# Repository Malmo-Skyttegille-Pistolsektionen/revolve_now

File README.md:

<h1></h1>

Software for running timed shooting programs on a rotating target system, built
by and for Malmö Skyttegille Pistolsektionen.

An ESP32-S3 board turns the targets face-on and edge-on to a shooting program
and plays the spoken range commands over an amplifier. A React web app — served
by the board itself over WiFi — starts and stops programs, follows the run live
over Server-Sent Events, and manages the stored programs and audio.

## ⚠️ SAFETY WARNING — READ BEFORE INSTALLING OR OPERATING

**This device moves steel on a live firing range, and it moves it on a timer.**
A target turns because a program said it was time, not because it can see who
is in front of it. It has no idea anyone is downrange.

- **The range's own safety rules and range commands govern the line. This
  software governs nothing.** A program running is not a range that is hot; a
  program stopped is not a range that is safe.
- **NEVER go downrange because the web app says the run has finished.** Confirm
  a cease-fire the way your range already requires — verbally, with firearms
  cleared and benched.
- **NEVER leave the device powered while people are forward of the firing
  line** unless your club has decided that is safe and knows what the targets
  do at power-up.
- **A target turning can injure somebody standing next to it.** Keep clear of
  the mechanism whenever the device is powered.

The targets rest **shown** at boot, deliberately: a target that turns of its own
accord when a board is powered is the failure this project is most concerned
with. That resting state can be changed to suit a target system wired the other
way round, but only over a USB cable, never from the web app — see
[Expert mode](https://malmo-skyttegille-pistolsektionen.github.io/revolve_now/expert-mode/).

**Do not rely on this software to protect anyone.** It is a convenience for
running programs, not a safety device, and it has no interlock, no sensor, and
no way to know where people are.

**LIABILITY DISCLAIMER:** This project is provided as-is with absolutely no
warranty of any kind. The author(s) accept no responsibility or liability for
any injury, damage, or loss resulting from building, installing, modifying, or
operating this system. You build and use it entirely at your own risk.

---

## Documentation

Everything an operator needs is on the documentation site, in English and
Swedish (the language menu in the header switches):

- **[Operator documentation](https://malmo-skyttegille-pistolsektionen.github.io/revolve_now/)**
  — wiring, connecting, running a program, settings, and what the status LED is
  telling you. This is the one to send a club member.
- **[Program editor](https://malmo-skyttegille-pistolsektionen.github.io/revolve_now/editor/)**
  — write and edit programs in a browser with **no device attached**, then
  download the file or open a pull request against this repository. Also useful
  for reading a shipped program without a board in front of you.
- **[Hardware and wiring](https://malmo-skyttegille-pistolsektionen.github.io/revolve_now/hardware/)**
  — what a target system has to do to work, the DB9 pinout, and the transistor
  that does the switching.

## Installing

Releases ship a pre-built firmware image; you do not need a toolchain to put it
on a board. See
[Connecting](https://malmo-skyttegille-pistolsektionen.github.io/revolve_now/connecting/)
for getting the device onto your network afterwards, and
[Settings](https://malmo-skyttegille-pistolsektionen.github.io/revolve_now/settings/)
for adapting a stock image to your own board — the target pin, its polarity,
the audio and LED pins and the device's name are all configurable on the
device, without rebuilding it.

## Target systems

- **[Eigenbrod TP2](https://eigenbrod-schiessanlagen.de/en/products?tx_produkt_produkte%5Baction%5D=show&tx_produkt_produkte%5BL%5D=2&tx_produkt_produkte%5Bprodukt%5D=319&cHash=942340d5971be0a0ac3d26ff3c257c0b)**
  — what this was built against and what it runs on.

Nothing in the firmware is specific to that system. The board speaks no
proprietary protocol to the targets: it closes and opens **one circuit**, and
the target system's own electronics do the rest. Any system driven the same way
should work.

## Layout

| Directory | Holds |
|---|---|
| [`contracts/`](contracts/README.md) | The canonical API contract: OpenAPI for REST v2, AsyncAPI for SSE v2, the program schema |
| [`firmware/`](firmware/README.md) | The ESP-IDF firmware: target IO, audio, storage, REST + SSE server |
| [`webapp/`](webapp/README.md) | The React front end, embedded in the firmware's application image |
| [`resources/`](resources/README.md) | Shipped programs and audio clips flashed onto the device |
| [`hardware/enclosure/`](hardware/enclosure/README.md) | A 3D-printable box for the rev 2 main board |
| [`docs/`](docs/) | The [decision log](docs/DECISIONS.md), [how releases are cut](docs/RELEASING.md), and the source of the documentation site |

## Contributing

Building, flashing, running it without a device, and the coding standards are
in [`CONTRIBUTING.md`](CONTRIBUTING.md).

## License

MIT — see [`LICENSE`](LICENSE). It covers everything here except the vendored
libraries under `firmware/lib/`, which keep their own.

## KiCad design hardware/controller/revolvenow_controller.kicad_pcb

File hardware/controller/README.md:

# Controller board

The Revolve Now controller board (the relay box), rev 2. It has no
microcontroller: eight LGE2300 N-channel MOSFETs (`Q1`–`Q8`) switch the target
outputs low, driven from the inputs on `J9`. The board is two halves, labelled
**1–2** and **3–4** on the silkscreen, each with its own USB-C power input,
output RJ45 and output header. 95 × 50 mm, two copper layers.

## Connectors

| Ref | Part | Role |
|---|---|---|
| `J3` | RJ45 | Outputs of half 1–2: the drains of `Q1`–`Q4` on pins 1, 3, 5, 7, ground on 2, 4, 6, 8 |
| `J5` | RJ45 | Outputs of half 3–4, the same way, from `Q5`–`Q8` |
| `J4`, `J6` | 1×6 pin header | +5 V, GND and the four outputs of half 1–2 and 3–4 |
| `J7`, `J8` | USB-C | 5 V power for half 1–2 and 3–4. Power only: the data lines are not connected |
| `J9` | RJ45 | Manual remote control: +5 V on pins 1, 3, 5, 7, MOSFET gates on 2, 4, 6, 8 |
| `J1`, `J2` | 2×2 pin header | Jumpers that join the +5 V (`J1`) and the GND (`J2`) of the two halves. `R1` and `R2`, 0 Ω and not fitted, do the same |

Each `J9` pair drives two MOSFETs, so one input switches two outputs:

| `J9` pins | MOSFETs | Outputs |
|---|---|---|
| 1–2 | `Q1`, `Q3` | `J3` pins 1 and 5 |
| 3–4 | `Q2`, `Q4` | `J3` pins 3 and 7 |
| 5–6 | `Q5`, `Q7` | `J5` pins 1 and 5 |
| 7–8 | `Q6`, `Q8` | `J5` pins 3 and 7 |

## Files

| Path | What it is |
|---|---|
| `revolvenow_controller.kicad_pro` | The KiCad project. Open this one, in KiCad 10 |
| `revolvenow_controller.kicad_sch` | Root schematic: the Controller sheet, and `power1.kicad_sch` and `output1.kicad_sch` each used twice, once per half |
| `revolvenow_controller.kicad_pcb` | The board |
| `fab/rev2/` | What was sent to the fab, described in the [hardware README](../README.md#fabrication-output) |

Footprints from the shared library come from [`../lib/`](../lib/) through
`fp-lib-table`.

Open items in the design are tracked in the
[rev 2 review on #603](https://github.com/Malmo-Skyttegille-Pistolsektionen/revolve_now/pull/603#issuecomment-6858837484).

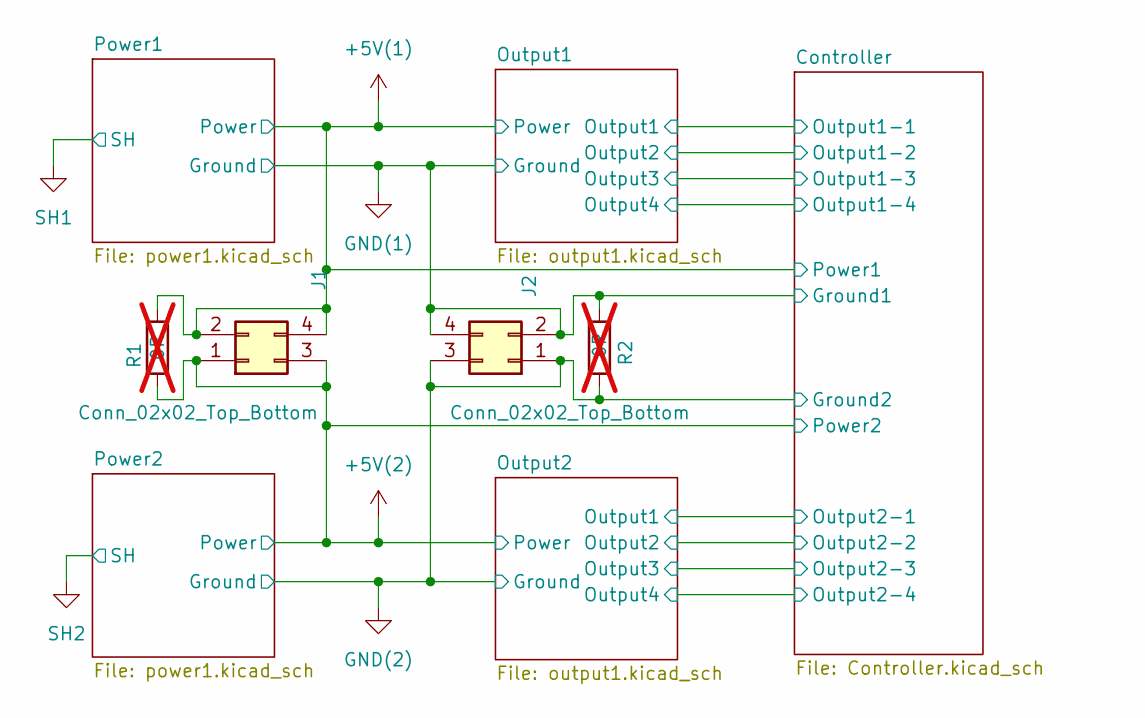
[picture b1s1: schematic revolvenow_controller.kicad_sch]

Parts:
J1, J2: Conn_02x02_Top_Bottom; PinHeader_2x02_P2.54mm_Vertical
R1, R2: 0R; R_0603_1608Metric_Pad0.98x0.95mm_HandSolder; not fitted

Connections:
+5V(1): J1.2, J1.4, R1.1; also elsewhere on the board
+5V(2): J1.1, J1.3, R1.2; also elsewhere on the board
GND(1): J2.2, J2.4, R2.2; also elsewhere on the board
GND(2): J2.1, J2.3, R2.1; also elsewhere on the board

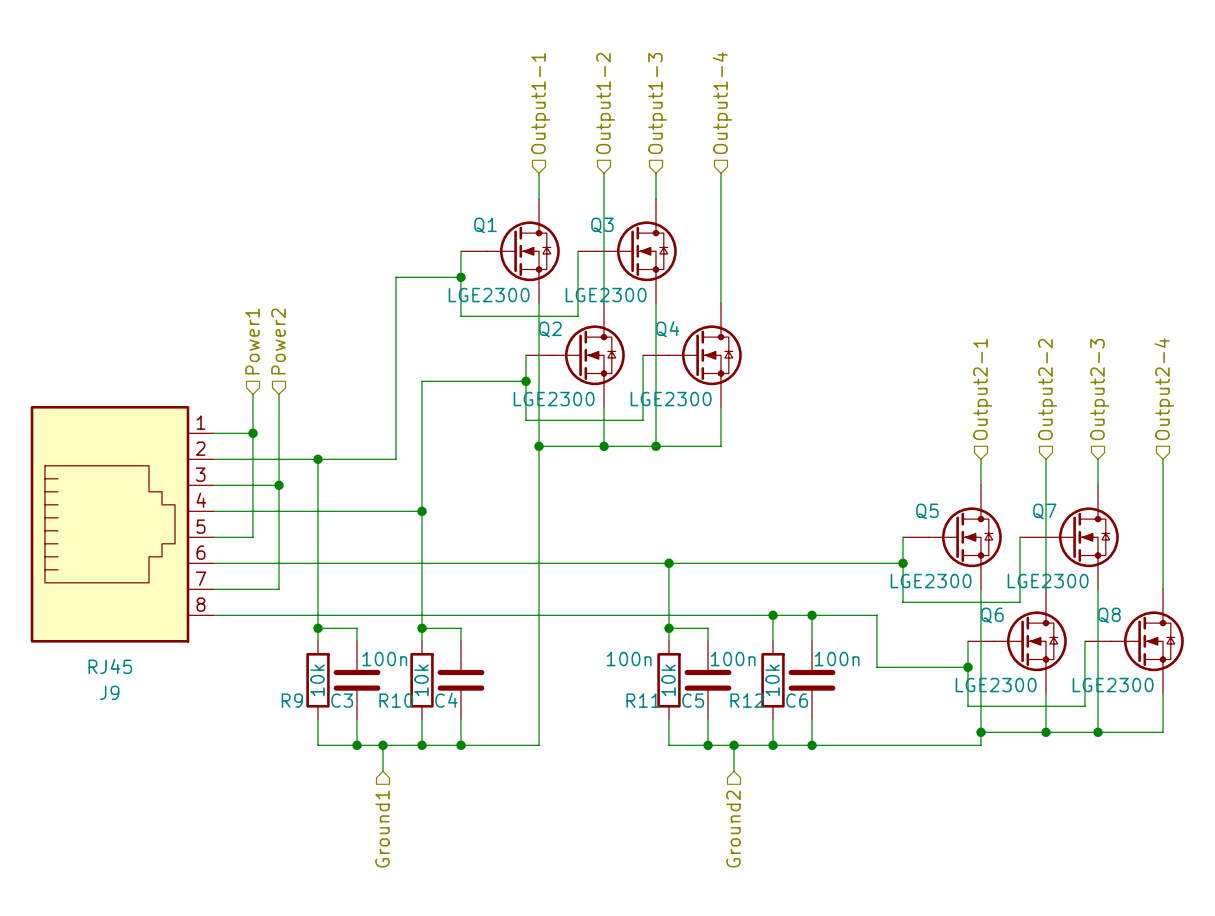
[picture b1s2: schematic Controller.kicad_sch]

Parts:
C3, C4, C5, C6: 100n; C_0603_1608Metric_Pad1.08x0.95mm_HandSolder
J9: RJ45
Q1, Q2, Q3, Q4, Q5, Q6, Q7, Q8: LGE2300; SOT-23
R9, R10, R11, R12: 10k; R_0603_1608Metric_Pad0.98x0.95mm_HandSolder

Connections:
+5V(1): J9.1, J9.5; also elsewhere on the board
+5V(2): J9.3, J9.7; also elsewhere on the board
/Controller/Output1-1: Q1.3 (D); also elsewhere on the board
/Controller/Output1-2: Q2.3 (D); also elsewhere on the board
/Controller/Output1-3: Q3.3 (D); also elsewhere on the board
/Controller/Output1-4: Q4.3 (D); also elsewhere on the board
/Controller/Output2-1: Q5.3 (D); also elsewhere on the board
/Controller/Output2-2: Q6.3 (D); also elsewhere on the board
/Controller/Output2-3: Q7.3 (D); also elsewhere on the board
/Controller/Output2-4: Q8.3 (D); also elsewhere on the board
GND(1): C3.2, C4.2, Q1.2 (S), Q2.2 (S), Q3.2 (S), Q4.2 (S), R9.1, R10.1; also elsewhere on the board
GND(2): C5.2, C6.1, Q5.2 (S), Q6.2 (S), Q7.2 (S), Q8.2 (S), R11.1, R12.1; also elsewhere on the board
unnamed: C3.1, J9.2, Q1.1 (G), Q3.1 (G), R9.2
unnamed: C4.1, J9.4, Q2.1 (G), Q4.1 (G), R10.2
unnamed: C5.1, J9.6, Q5.1 (G), Q7.1 (G), R11.2
unnamed: C6.2, J9.8, Q6.1 (G), Q8.1 (G), R12.2

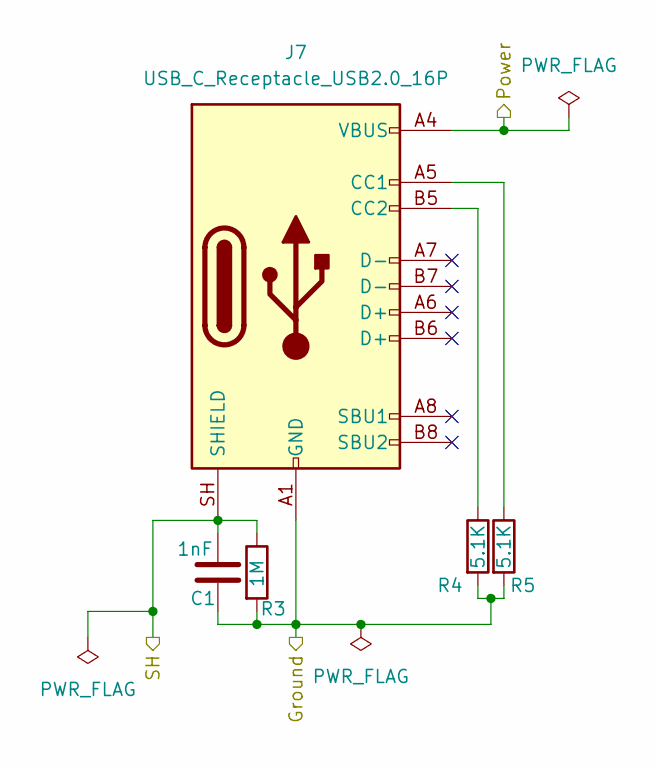
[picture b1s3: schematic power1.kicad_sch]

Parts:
C1: 1nF; C_0603_1608Metric_Pad1.08x0.95mm_HandSolder
J7: USB_C_Receptacle_USB2.0_16P; USB Type-C-02
R3: 1M; R_0603_1608Metric_Pad0.98x0.95mm_HandSolder
R4, R5: 5.1K; R_0603_1608Metric_Pad0.98x0.95mm_HandSolder

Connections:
+5V(1): J7.A4 (VBUS), J7.B4 (VBUS); also elsewhere on the board
GND(1): C1.2, J7.A1 (GND), J7.B1 (GND), R3.2, R4.2, R5.2; also elsewhere on the board
unnamed: J7.A5 (CC1), R5.1
unnamed: J7.B5 (CC2), R4.1
SH1: C1.1, J7.SH (SHIELD), R3.1

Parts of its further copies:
C2: 1nF; C_0603_1608Metric_Pad1.08x0.95mm_HandSolder
J8: USB_C_Receptacle_USB2.0_16P; USB Type-C-02
R6: 1M; R_0603_1608Metric_Pad0.98x0.95mm_HandSolder
R7, R8: 5.1K; R_0603_1608Metric_Pad0.98x0.95mm_HandSolder

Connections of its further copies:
+5V(2): J8.A4 (VBUS), J8.B4 (VBUS); also elsewhere on the board
GND(2): C2.2, J8.A1 (GND), J8.B1 (GND), R6.2, R7.2, R8.2; also elsewhere on the board
unnamed: J8.A5 (CC1), R8.1
unnamed: J8.B5 (CC2), R7.1
SH2: C2.1, J8.SH (SHIELD), R6.1

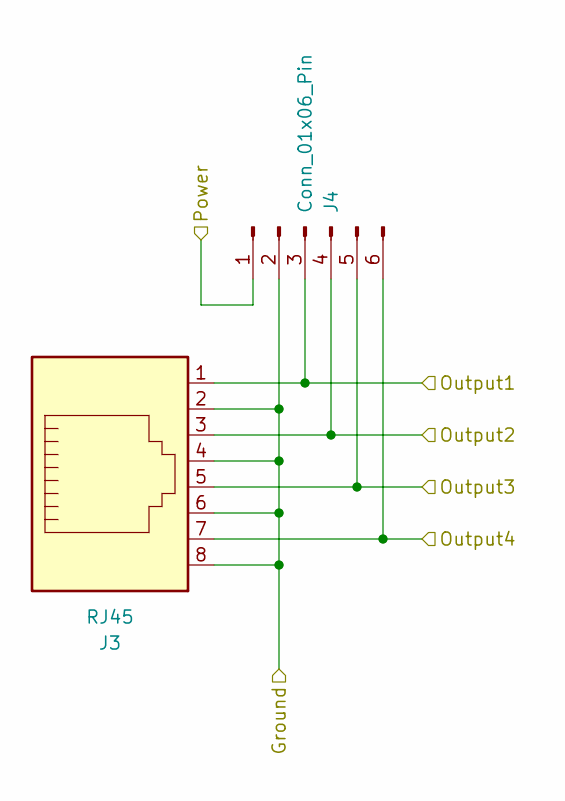
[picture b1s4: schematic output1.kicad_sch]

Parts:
J3: RJ45
J4: Conn_01x06_Pin; PinHeader_1x06_P2.54mm_Vertical

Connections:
+5V(1): J4.1; also elsewhere on the board
/Controller/Output1-1: J3.1, J4.3; also elsewhere on the board
/Controller/Output1-2: J3.3, J4.4; also elsewhere on the board
/Controller/Output1-3: J3.5, J4.5; also elsewhere on the board
/Controller/Output1-4: J3.7, J4.6; also elsewhere on the board
GND(1): J3.2, J3.4, J3.6, J3.8, J4.2; also elsewhere on the board

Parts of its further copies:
J5: RJ45
J6: Conn_01x06_Pin; PinHeader_1x06_P2.54mm_Vertical

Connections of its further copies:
+5V(2): J6.1; also elsewhere on the board
/Controller/Output2-1: J5.1, J6.3; also elsewhere on the board
/Controller/Output2-2: J5.3, J6.4; also elsewhere on the board
/Controller/Output2-3: J5.5, J6.5; also elsewhere on the board
/Controller/Output2-4: J5.7, J6.6; also elsewhere on the board
GND(2): J5.2, J5.4, J5.6, J5.8, J6.2; also elsewhere on the board

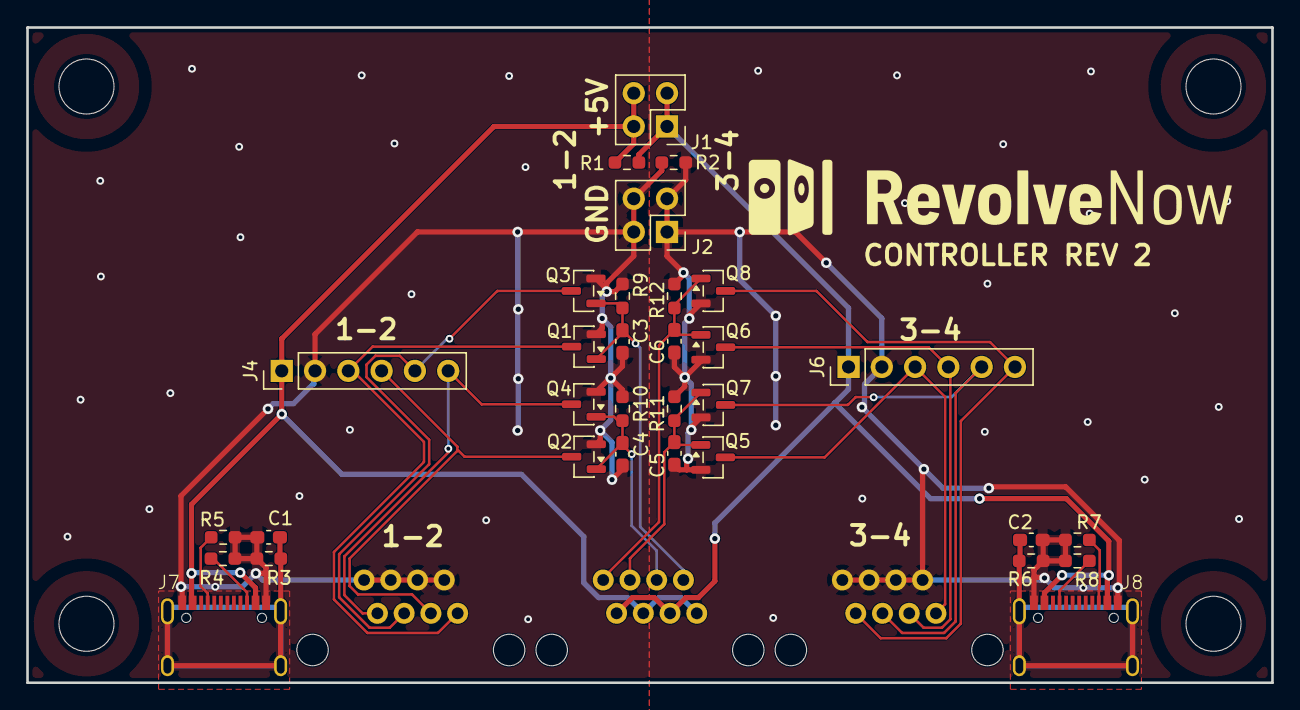
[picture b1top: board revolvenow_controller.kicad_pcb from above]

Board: 2 copper layers, 95.0 x 50.0 mm, 35 parts (0 on the bottom side), 22 nets.

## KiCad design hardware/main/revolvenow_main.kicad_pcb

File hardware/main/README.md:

# Main board

The Revolve Now main board, rev 2. An ESP32-S3-WROOM-1 (`U1`) drives sixteen
opto-isolated target outputs, reads two opto-isolated trigger inputs, talks to
the network over WiFi or a W5500 Ethernet controller (`U10`), and plays the
range commands through a PCM5102A DAC (`U2`). One WS2812B (`D8`) is the status
LED. 100 × 100 mm, two copper layers.

## Connectors

| Ref | Part | Role |
|---|---|---|
| `J1`, `J2`, `J6`, `J8` | RJ45 | Target outputs Turn 0–3, 4–7, 8–11 and 12–15, through the LTV-847 optocouplers `U4`, `U5`, `U7` and `U8` |
| `J3` | RJ45 | Trigger inputs through the LTV-847 `U3`: pins 1–2 for a 5 V signal, pins 3–6 for 12 V |
| `J4` | USB-C | 5 V power, and the ESP32-S3's native USB (GPIO19/20) behind the USBLC6-2SC6 `U12` |
| `J5` | 1×3 pin header | UART0: RX, GND, TX |
| `J7` | 3.5 mm jack (PJ-320A) | Line out from the DAC |
| `J9` | 2×3 pin header | Jumper that puts GPIO4 on the status LED data (pins 1–2), trigger 0 (3–4) or trigger 1 (5–6) |
| `U11` | RJ45 with magnetics (J0026D21BNL) | Ethernet, from the W5500 |

Each output RJ45 carries four outputs, one per twisted pair, each the
transistor side of one optocoupler channel with the collector on the odd pin:

| Pins | Output |
|---|---|
| 1–2 | first (Turn 0, 4, 8, 12) |
| 3–6 | second |
| 4–5 | third |
| 7–8 | fourth (Turn 3, 7, 11, 15) |

The two buttons are `SW2` (FLASH, on GPIO0) and `SW3` (RESET, on EN).

## Files

| Path | What it is |
|---|---|
| `revolvenow_main.kicad_pro` | The KiCad project. Open this one, in KiCad 10 |
| `revolvenow_main.kicad_sch` | Root schematic, with one sheet per function: ESP, Power, USB, Network, Audio, Output, Trigger, LED |
| `buttons.kicad_sch`, `flash.kicad_sch`, `temperature.kicad_sch` | Sheets no longer in the hierarchy |
| `revolvenow_main.kicad_pcb` | The board |
| `fab/rev2/` | What was sent to the fab, described in the [hardware README](../README.md#fabrication-output) |

Footprints from the shared library come from [`../lib/`](../lib/) through
`fp-lib-table`.

Open items in the design are tracked in the
[rev 2 review on #436](https://github.com/Malmo-Skyttegille-Pistolsektionen/revolve_now/pull/436#issuecomment-6858836932).

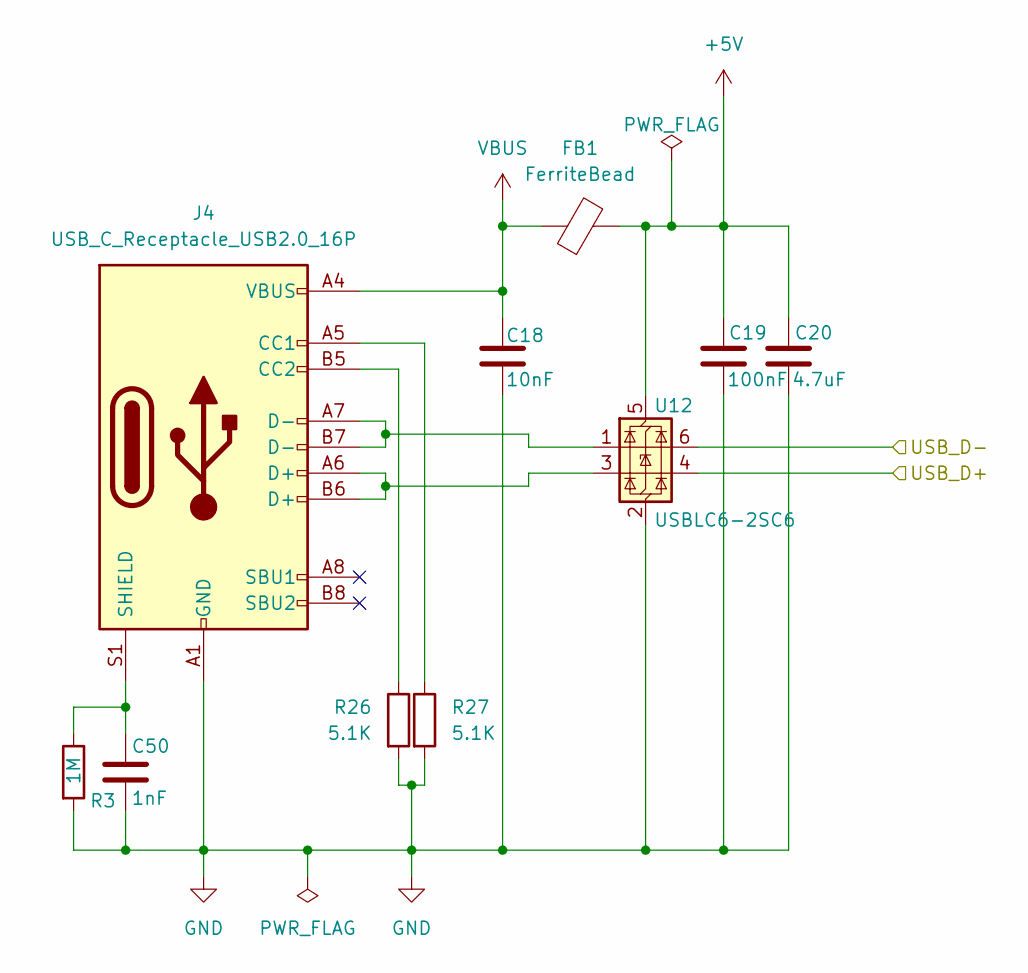
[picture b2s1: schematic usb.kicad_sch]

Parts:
C18: 10nF; C_0603_1608Metric_Pad1.08x0.95mm_HandSolder
C19: 100nF; C_0603_1608Metric_Pad1.08x0.95mm_HandSolder
C20: 4.7uF; C_0603_1608Metric_Pad1.08x0.95mm_HandSolder
C50: 1nF; C_0603_1608Metric_Pad1.08x0.95mm_HandSolder
FB1: FerriteBead; R_0805_2012Metric_Pad1.20x1.40mm_HandSolder
J4: USB_C_Receptacle_USB2.0_16P; USB Type-C-02
R3: 1M; R_0603_1608Metric_Pad0.98x0.95mm_HandSolder
R26, R27: 5.1K; R_0603_1608Metric_Pad0.98x0.95mm_HandSolder
U12: USBLC6-2SC6; SOT-23-6

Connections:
+5V: C19.1, C20.1, FB1.2, U12.5 (VBUS); also elsewhere on the board
/ESP/USB_D+: U12.4 (I/O2); also elsewhere on the board
/ESP/USB_D-: U12.6 (I/O1); also elsewhere on the board
GND: C18.2, C19.2, C20.2, C50.1, J4.A1 (GND), J4.B1 (GND), R3.2, R26.2, R27.2, U12.2 (GND); also elsewhere on the board
unnamed: J4.A5 (CC1), R27.1
unnamed: J4.B5 (CC2), R26.1
unnamed: J4.A6 (D+), J4.B6 (D+), U12.3 (I/O2)
unnamed: J4.A7 (D-), J4.B7 (D-), U12.1 (I/O1)
unnamed: C50.2, J4.S1 (SHIELD), R3.1
VBUS: C18.1, FB1.1, J4.A4 (VBUS), J4.B4 (VBUS)

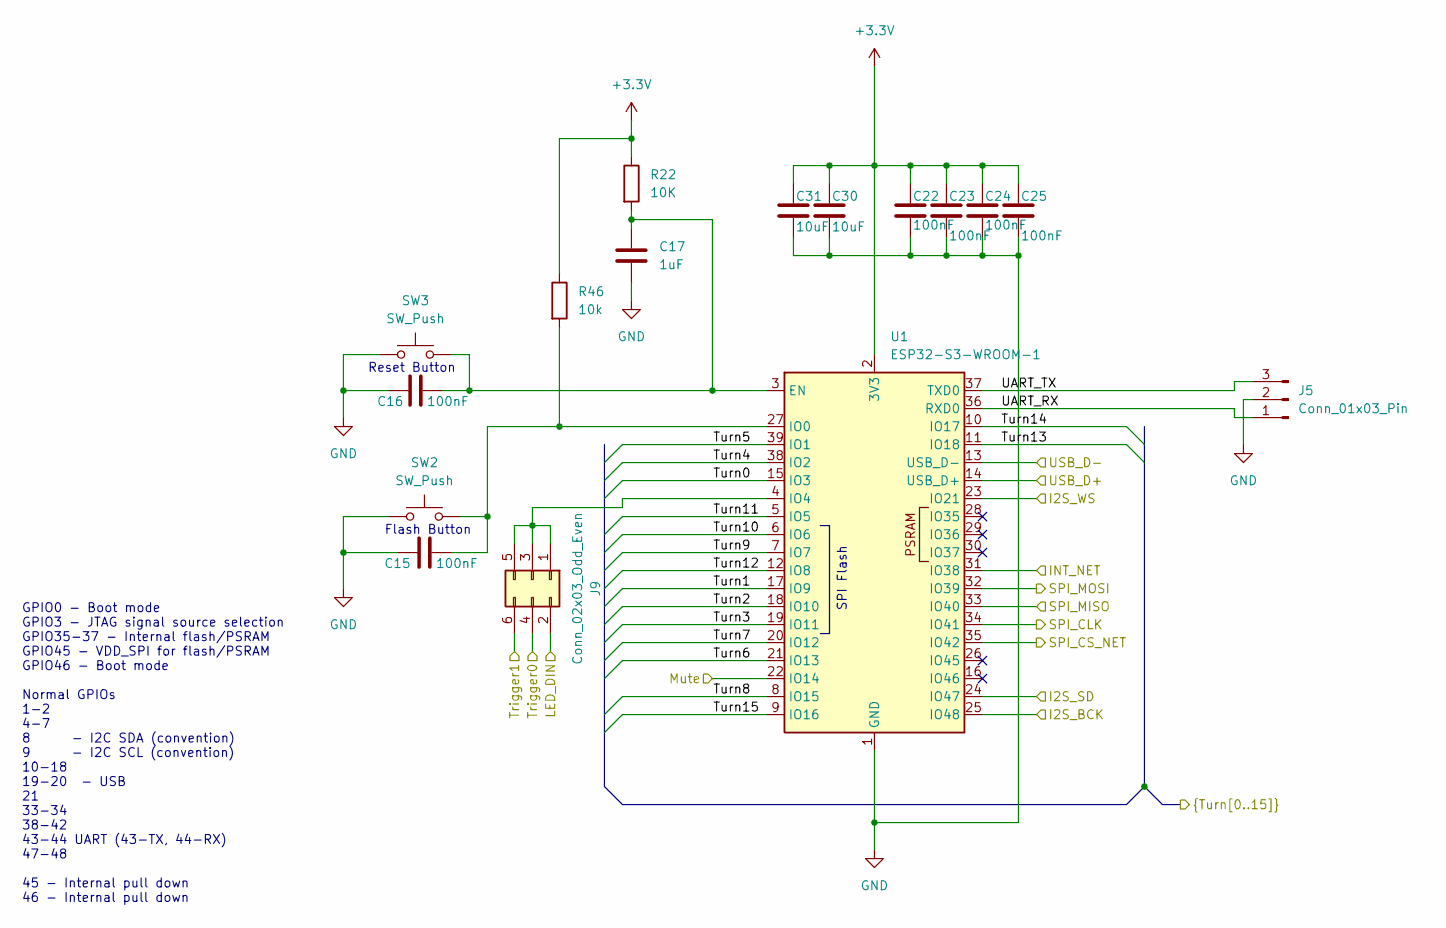
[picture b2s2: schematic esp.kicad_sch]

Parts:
C15, C16, C22, C23, C24, C25: 100nF; C_0603_1608Metric_Pad1.08x0.95mm_HandSolder
C17: 1uF; C_0603_1608Metric_Pad1.08x0.95mm_HandSolder
C30, C31: 10uF; C_0603_1608Metric_Pad1.08x0.95mm_HandSolder
J5: Conn_01x03_Pin; PinHeader_1x03_P2.54mm_Vertical
J9: Conn_02x03_Odd_Even; PinHeader_2x03_P2.54mm_Vertical
R22: 10K; R_0603_1608Metric_Pad0.98x0.95mm_HandSolder
R46: 10k; R_0603_1608Metric_Pad0.98x0.95mm_HandSolder
SW2, SW3: SW_Push; SW_SPST_PTS645Sx43SMTR92
U1: ESP32-S3-WROOM-1

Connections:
+3.3V: C22.1, C23.1, C24.1, C25.1, C30.1, C31.1, R22.1, R46.1, U1.2 (3V3); also elsewhere on the board
/Audio/BCK: U1.25 (IO48); also elsewhere on the board
/Audio/Mute: U1.22 (IO14); also elsewhere on the board
/Audio/SD: U1.24 (IO47); also elsewhere on the board
/Audio/WS: U1.23 (IO21); also elsewhere on the board
/ESP/INT_NET: U1.31 (IO38); also elsewhere on the board
/ESP/LED_DIN: J9.2; also elsewhere on the board
/ESP/SPI_CLK: U1.34 (IO41); also elsewhere on the board
/ESP/SPI_CS_NET: U1.35 (IO42); also elsewhere on the board
/ESP/SPI_MISO: U1.33 (IO40); also elsewhere on the board
/ESP/SPI_MOSI: U1.32 (IO39); also elsewhere on the board
/ESP/Trigger0: J9.4; also elsewhere on the board
/ESP/Trigger1: J9.6; also elsewhere on the board
/ESP/Turn0: U1.15 (IO3); also elsewhere on the board
/ESP/Turn1: U1.17 (IO9); also elsewhere on the board
/ESP/Turn2: U1.18 (IO10); also elsewhere on the board
/ESP/Turn3: U1.19 (IO11); also elsewhere on the board
/ESP/Turn4: U1.38 (IO2); also elsewhere on the board
/ESP/Turn5: U1.39 (IO1); also elsewhere on the board
/ESP/Turn6: U1.21 (IO13); also elsewhere on the board
/ESP/Turn7: U1.20 (IO12); also elsewhere on the board
/ESP/Turn8: U1.8 (IO15); also elsewhere on the board
/ESP/Turn9: U1.7 (IO7); also elsewhere on the board
/ESP/Turn10: U1.6 (IO6); also elsewhere on the board
/ESP/Turn11: U1.5 (IO5); also elsewhere on the board
/ESP/Turn12: U1.12 (IO8); also elsewhere on the board
/ESP/Turn13: U1.11 (IO18); also elsewhere on the board
/ESP/Turn14: U1.10 (IO17); also elsewhere on the board
/ESP/Turn15: U1.9 (IO16); also elsewhere on the board
/ESP/UART_RX: J5.1, U1.36 (RXD0)
/ESP/UART_TX: J5.3, U1.37 (TXD0)
/ESP/USB_D+: U1.14 (USB_D+); also elsewhere on the board
/ESP/USB_D-: U1.13 (USB_D-); also elsewhere on the board
GND: C15.1, C16.1, C17.2, C22.2, C23.2, C24.2, C25.2, C30.2, C31.2, J5.2, SW2.1, SW3.2, U1.1 (GND), U1.40 (GND), U1.41 (GND); also elsewhere on the board
unnamed: J9.1, J9.3, J9.5, U1.4 (IO4)
unnamed: C16.2, C17.1, R22.2, SW3.1, U1.3 (EN)
unnamed: C15.2, R46.2, SW2.2, U1.27 (IO0)

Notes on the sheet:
SPI Flash
Reset Button
Flash Button
GPIO0 - Boot mode GPIO3 - JTAG signal source selection GPIO35-37 - Internal flash/PSRAM GPIO45 - VDD_SPI for flash/PSRAM GPIO46 - Boot mode Normal GPIOs 1-2 4-7 8 - I2C SDA (convention) 9 - I2C SCL (convention) 10-18 19-20 - USB 21 33-34 38-42 43-44 UART (43-TX, 44-RX) 47-48 45 - Internal pull down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

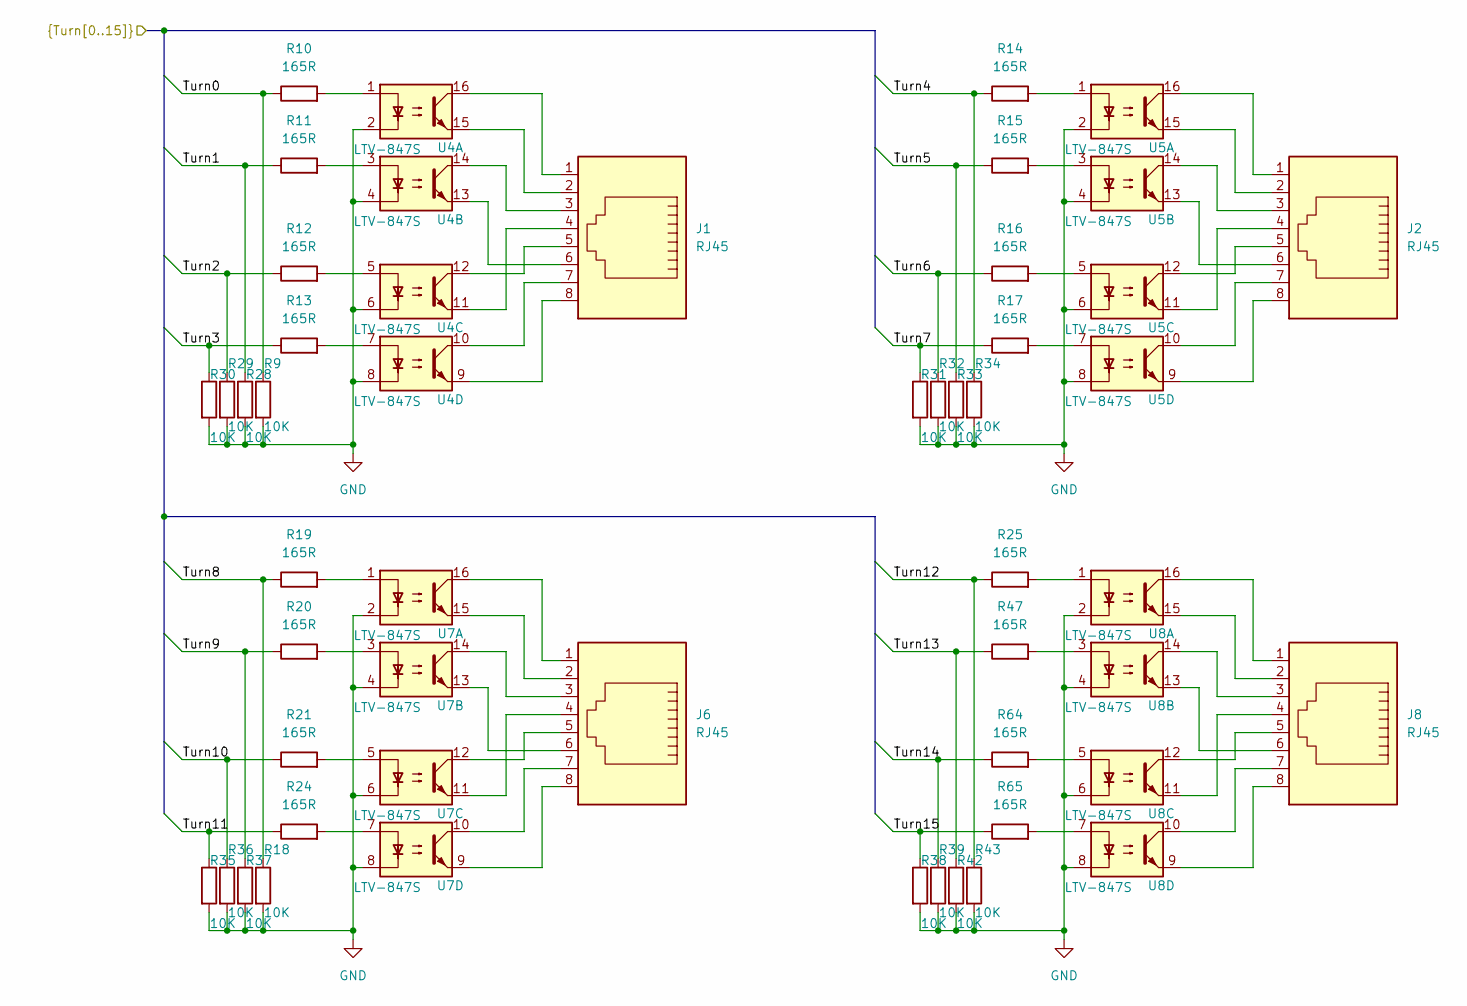
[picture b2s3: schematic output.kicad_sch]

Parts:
J1, J2, J6, J8: RJ45
R9, R18, R28, R29, R30, R31, R32, R33, R34, R35, R36, R37, R38, R39, R42, R43: 10K; R_0603_1608Metric_Pad0.98x0.95mm_HandSolder
R10, R11, R12, R13, R14, R15, R16, R17, R19, R20, R21, R24, R25, R47, R64, R65: 165R; R_0603_1608Metric_Pad0.98x0.95mm_HandSolder
U4, U5, U7, U8: LTV-847S; SMDIP-16_W9.53mm

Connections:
/ESP/Turn0: R9.1, R10.1; also elsewhere on the board
/ESP/Turn1: R11.1, R28.1; also elsewhere on the board
/ESP/Turn2: R12.1, R29.1; also elsewhere on the board
/ESP/Turn3: R13.1, R30.1; also elsewhere on the board
/ESP/Turn4: R14.1, R34.1; also elsewhere on the board
/ESP/Turn5: R15.1, R33.1; also elsewhere on the board
/ESP/Turn6: R16.1, R32.1; also elsewhere on the board
/ESP/Turn7: R17.1, R31.1; also elsewhere on the board
/ESP/Turn8: R18.1, R19.1; also elsewhere on the board
/ESP/Turn9: R20.1, R37.1; also elsewhere on the board
/ESP/Turn10: R21.1, R36.1; also elsewhere on the board
/ESP/Turn11: R24.1, R35.1; also elsewhere on the board
/ESP/Turn12: R25.1, R43.1; also elsewhere on the board
/ESP/Turn13: R42.1, R47.1; also elsewhere on the board
/ESP/Turn14: R39.1, R64.1; also elsewhere on the board
/ESP/Turn15: R38.1, R65.1; also elsewhere on the board
GND: R9.2, R18.2, R28.2, R29.2, R30.2, R31.2, R32.2, R33.2, R34.2, R35.2, R36.2, R37.2, R38.2, R39.2, R42.2, R43.2, U4.2, U4.4, U4.6, U4.8, U5.2, U5.4, U5.6, U5.8, U7.2, U7.4, U7.6, U7.8, U8.2, U8.4, U8.6, U8.8; also elsewhere on the board
unnamed: J1.1, U4.16
unnamed: J1.2, U4.15
unnamed: J1.3, U4.14
unnamed: J1.4, U4.11
unnamed: J1.5, U4.12
unnamed: J1.6, U4.13
unnamed: J1.7, U4.10
unnamed: J1.8, U4.9
unnamed: J2.1, U5.16
unnamed: J2.2, U5.15
unnamed: J2.3, U5.14
unnamed: J2.4, U5.11
unnamed: J2.5, U5.12
unnamed: J2.6, U5.13
unnamed: J2.7, U5.10
unnamed: J2.8, U5.9
unnamed: J6.1, U7.16
unnamed: J6.2, U7.15
unnamed: J6.3, U7.14
unnamed: J6.4, U7.11
unnamed: J6.5, U7.12
unnamed: J6.6, U7.13
unnamed: J6.7, U7.10
unnamed: J6.8, U7.9
unnamed: J8.1, U8.16
unnamed: J8.2, U8.15
unnamed: J8.3, U8.14
unnamed: J8.4, U8.11
unnamed: J8.5, U8.12
unnamed: J8.6, U8.13
unnamed: J8.7, U8.10
unnamed: J8.8, U8.9
unnamed: R10.2, U4.1
unnamed: R11.2, U4.3
unnamed: R12.2, U4.5
unnamed: R13.2, U4.7
unnamed: R14.2, U5.1
unnamed: R15.2, U5.3
unnamed: R16.2, U5.5
unnamed: R17.2, U5.7
unnamed: R19.2, U7.1
unnamed: R20.2, U7.3
unnamed: R21.2, U7.5
unnamed: R24.2, U7.7
unnamed: R25.2, U8.1
unnamed: R47.2, U8.3
unnamed: R64.2, U8.5
unnamed: R65.2, U8.7

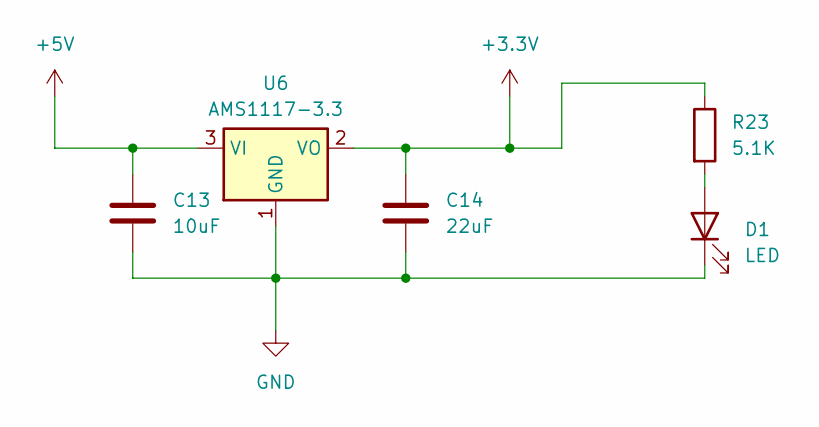
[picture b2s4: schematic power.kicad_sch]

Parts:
C13: 10uF; C_0603_1608Metric_Pad1.08x0.95mm_HandSolder
C14: 22uF; C_0603_1608Metric_Pad1.08x0.95mm_HandSolder
D1: LED; LED_0603_1608Metric_Pad1.05x0.95mm_HandSolder
R23: 5.1K; R_0603_1608Metric_Pad0.98x0.95mm_HandSolder
U6: AMS1117-3.3; SOT-223

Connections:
+3.3V: C14.1, R23.1, U6.2 (VO); also elsewhere on the board
+5V: C13.1, U6.3 (VI); also elsewhere on the board
GND: C13.2, C14.2, D1.1 (K), U6.1 (GND); also elsewhere on the board
unnamed: D1.2 (A), R23.2

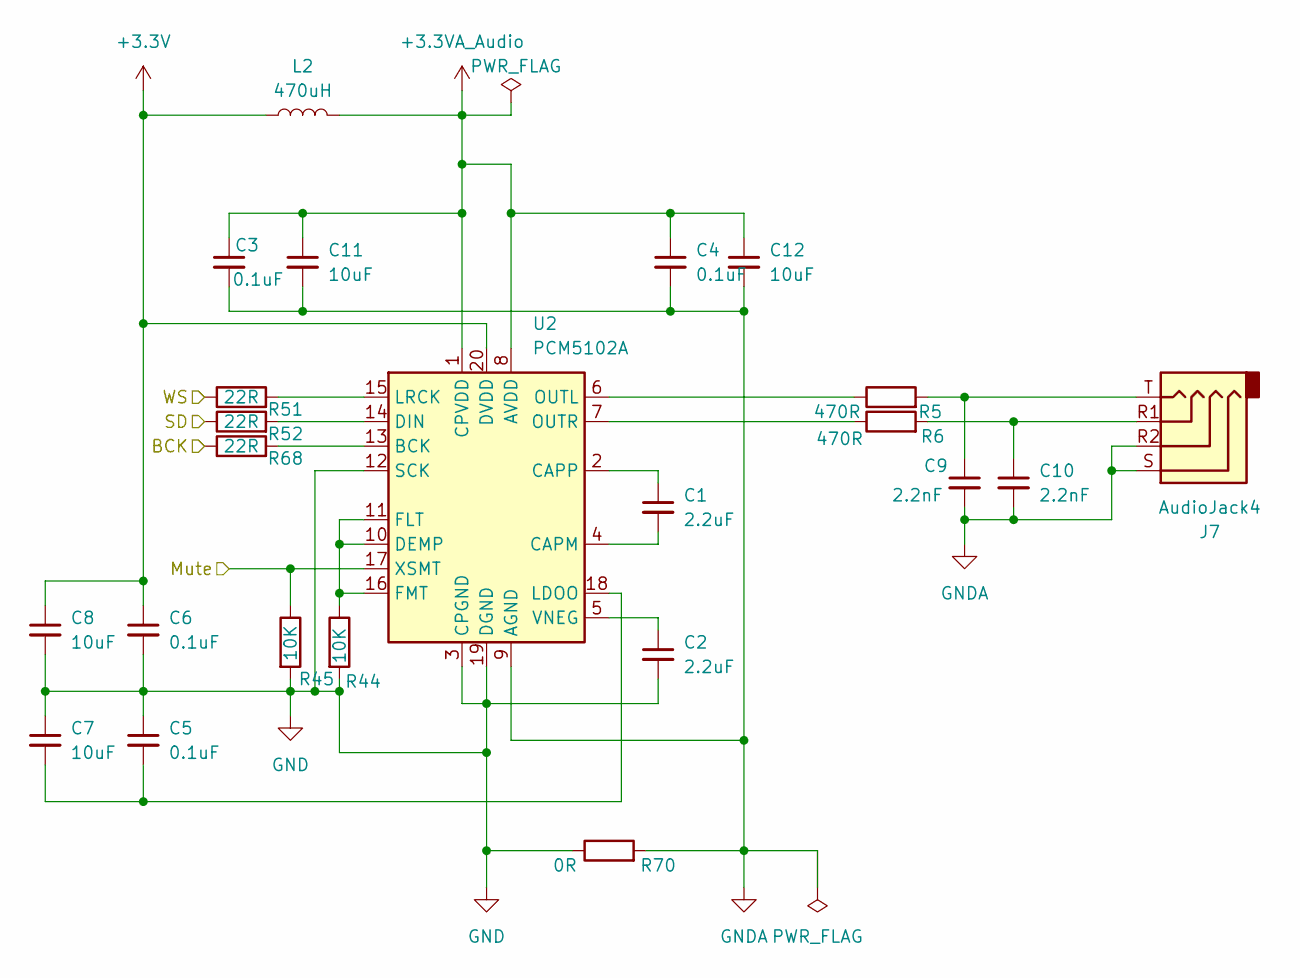
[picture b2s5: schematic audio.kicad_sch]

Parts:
C1, C2: 2.2uF; C_0603_1608Metric_Pad1.08x0.95mm_HandSolder
C3, C4, C5, C6: 0.1uF; C_0603_1608Metric_Pad1.08x0.95mm_HandSolder
C7, C8, C11, C12: 10uF; C_0603_1608Metric_Pad1.08x0.95mm_HandSolder
C9, C10: 2.2nF; C_0603_1608Metric_Pad1.08x0.95mm_HandSolder
J7: AudioJack4; AudioJack PJ-320A
L2: 470uH; L_1210_3225Metric_Pad1.42x2.65mm_HandSolder
R5, R6: 470R; R_0603_1608Metric_Pad0.98x0.95mm_HandSolder
R44, R45: 10K; R_0603_1608Metric_Pad0.98x0.95mm_HandSolder
R51, R52, R68: 22R; R_0603_1608Metric_Pad0.98x0.95mm_HandSolder
R70: 0R; R_0603_1608Metric_Pad0.98x0.95mm_HandSolder
U2: PCM5102A; TSSOP-20_4.4x6.5mm_P0.65mm

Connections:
+3.3V: C6.1, C8.1, L2.1, U2.20 (DVDD); also elsewhere on the board
+3.3VA_Audio: C3.1, C4.1, C11.1, C12.1, L2.2, U2.1 (CPVDD), U2.8 (AVDD)
/Audio/BCK: R68.1; also elsewhere on the board
/Audio/Mute: R45.1, U2.17 (XSMT); also elsewhere on the board
/Audio/SD: R52.1; also elsewhere on the board
/Audio/WS: R51.1; also elsewhere on the board
GND: C2.2, C5.1, C6.2, C7.1, C8.2, R44.2, R45.2, R70.1, U2.3 (CPGND), U2.12 (SCK), U2.19 (DGND); also elsewhere on the board
GNDA: C3.2, C4.2, C9.2, C10.2, C11.2, C12.2, J7.R2, J7.S, R70.2, U2.9 (AGND)
unnamed: C9.1, J7.T, R5.2
unnamed: C10.1, J7.R1, R6.2
unnamed: R68.2, U2.13 (BCK)
unnamed: C1.2, U2.4 (CAPM)
unnamed: C1.1, U2.2 (CAPP)
unnamed: R44.1, U2.10 (DEMP), U2.11 (FLT), U2.16 (FMT)
unnamed: R52.2, U2.14 (DIN)
unnamed: C5.2, C7.2, U2.18 (LDOO)
unnamed: R51.2, U2.15 (LRCK)
unnamed: R5.1, U2.6 (OUTL)
unnamed: R6.1, U2.7 (OUTR)
unnamed: C2.1, U2.5 (VNEG)

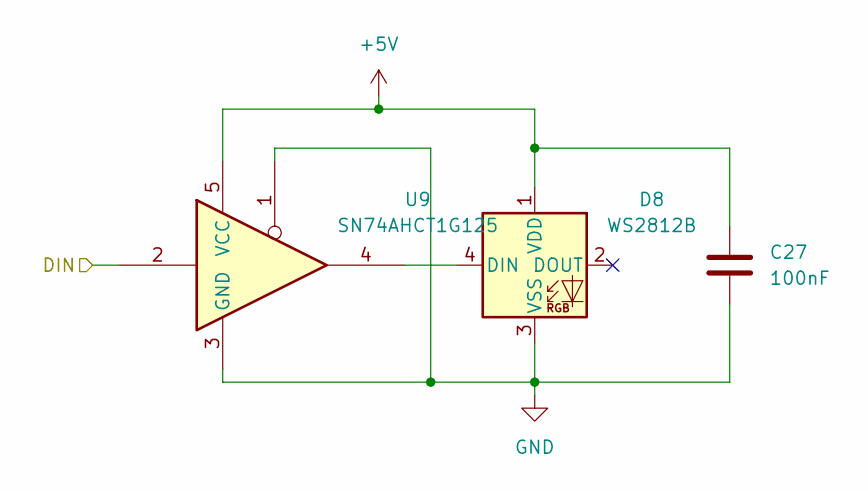
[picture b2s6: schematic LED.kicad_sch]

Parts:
C27: 100nF; C_0603_1608Metric_Pad1.08x0.95mm_HandSolder
D8: WS2812B; LED_WS2812B_PLCC4_5.0x5.0mm_P3.2mm
U9: SN74AHCT1G125; SOT-23-5

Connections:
+5V: C27.1, D8.1 (VDD), U9.5 (VCC); also elsewhere on the board
/ESP/LED_DIN: U9.2; also elsewhere on the board
GND: C27.2, D8.3 (VSS), U9.1, U9.3 (GND); also elsewhere on the board
unnamed: D8.4 (DIN), U9.4

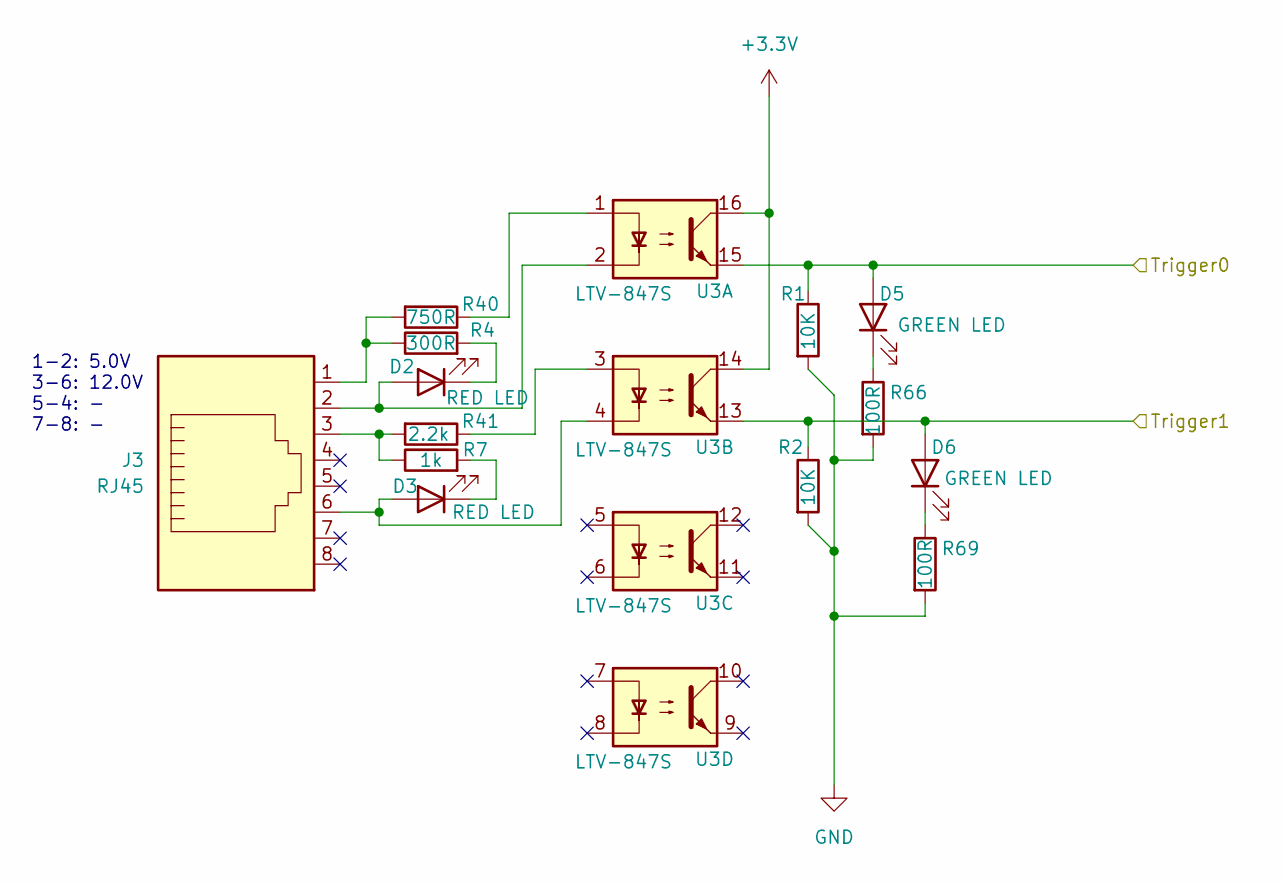
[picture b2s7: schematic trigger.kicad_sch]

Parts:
D2, D3: RED LED; LED_0603_1608Metric_Pad1.05x0.95mm_HandSolder
D5, D6: GREEN LED; LED_0603_1608Metric_Pad1.05x0.95mm_HandSolder
J3: RJ45
R1, R2: 10K; R_0603_1608Metric_Pad0.98x0.95mm_HandSolder
R4: 300R; R_0603_1608Metric_Pad0.98x0.95mm_HandSolder
R7: 1k; R_0603_1608Metric_Pad0.98x0.95mm_HandSolder
R40: 750R; R_0603_1608Metric_Pad0.98x0.95mm_HandSolder
R41: 2.2k; R_0603_1608Metric_Pad0.98x0.95mm_HandSolder
R66, R69: 100R; R_0603_1608Metric_Pad0.98x0.95mm_HandSolder
U3: LTV-847S; SMDIP-16_W9.53mm

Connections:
+3.3V: U3.14, U3.16; also elsewhere on the board
/ESP/Trigger0: D5.2 (A), R1.1, U3.15; also elsewhere on the board
/ESP/Trigger1: D6.2 (A), R2.1, U3.13; also elsewhere on the board
GND: R1.2, R2.2, R66.2, R69.2; also elsewhere on the board
unnamed: D2.2 (A), J3.2, U3.2
unnamed: D2.1 (K), R4.2
unnamed: D3.2 (A), J3.6, U3.4
unnamed: D3.1 (K), R7.2
unnamed: D5.1 (K), R66.1
unnamed: D6.1 (K), R69.1
unnamed: J3.1, R4.1, R40.2
unnamed: J3.3, R7.1, R41.2
unnamed: R40.1, U3.1
unnamed: R41.1, U3.3

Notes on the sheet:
1-2: 5.0V 3-6: 12.0V 5-4: - 7-8: -
